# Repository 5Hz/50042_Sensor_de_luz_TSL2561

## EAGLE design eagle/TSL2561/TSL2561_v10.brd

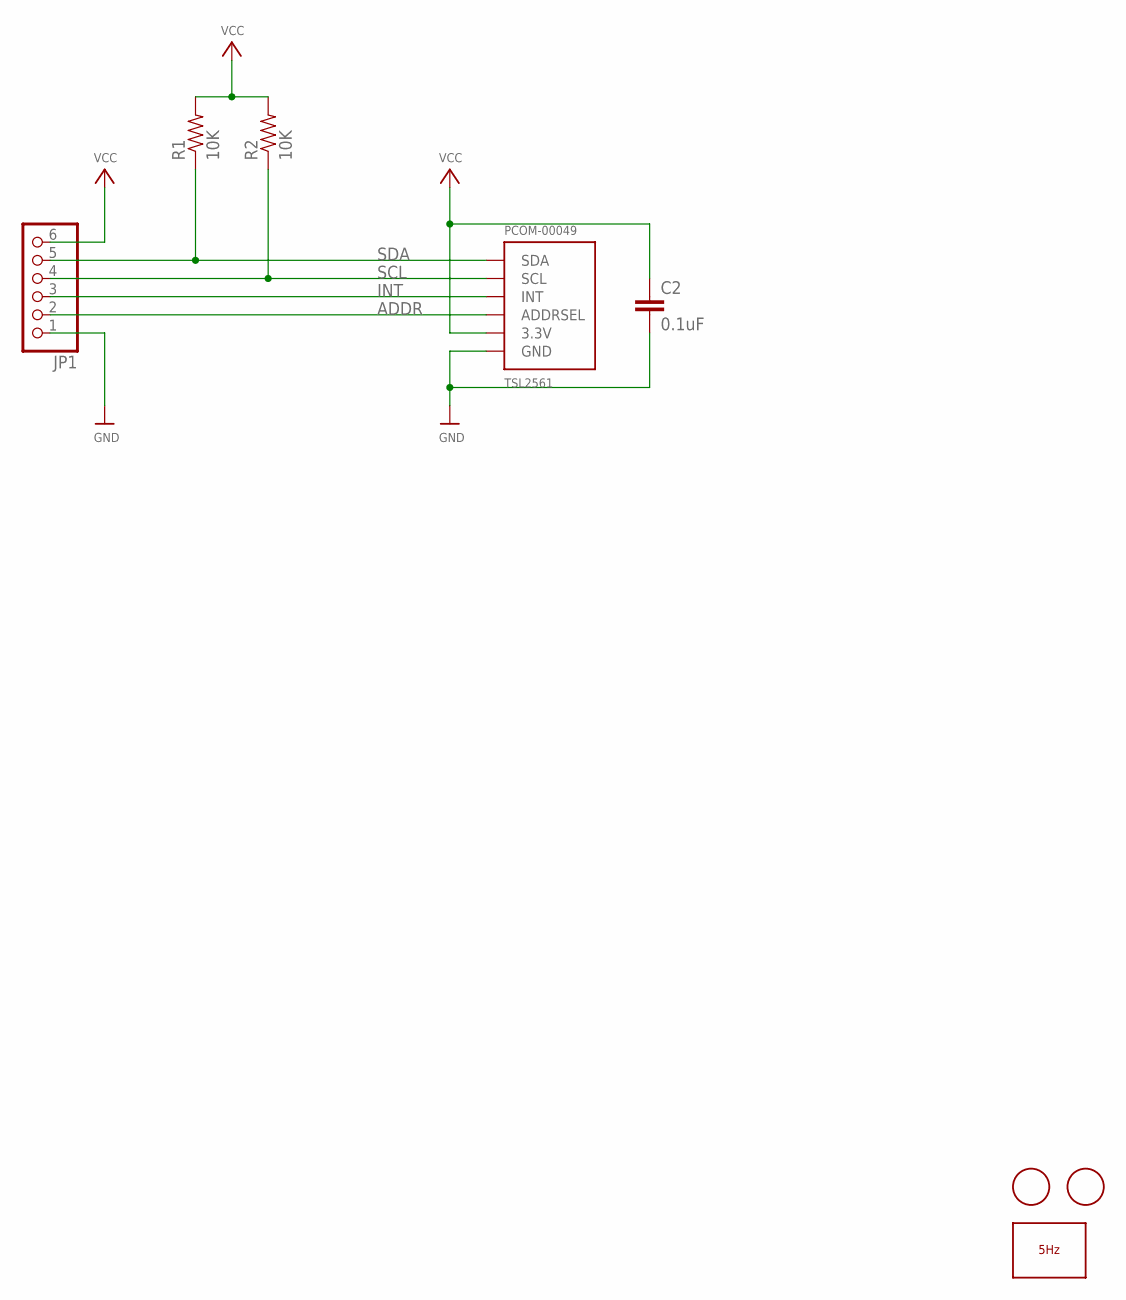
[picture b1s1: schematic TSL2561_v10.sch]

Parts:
C2: 0.1uF; 0603-CAP
JP1: HEADER-1X676MIL; 1X06_ROUND_76
LOGO1: LOGO_5HZ_MAIN_10MM; 5HZ_LOGO_MAIN_10MM
PCOM-00049: TSL2561; TSL2561_FN
R1, R2: 10K; 0603-RES
U$5, U$6: MOUNTINGHOLE2.0; MOUNTINGHOLE_2.0_PLATED

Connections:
ADDR: JP1.2, PCOM-00049.ADR (ADDRSEL)
GND: C2.2, JP1.1, PCOM-00049.VSS (GND)
INT: JP1.3, PCOM-00049.INT
SCL: JP1.4, PCOM-00049.CLK (SCL), R2.1
SDA: JP1.5, PCOM-00049.DATA (SDA), R1.1
VCC: C2.1, JP1.6, PCOM-00049.VDD (3.3V), R1.2, R2.2

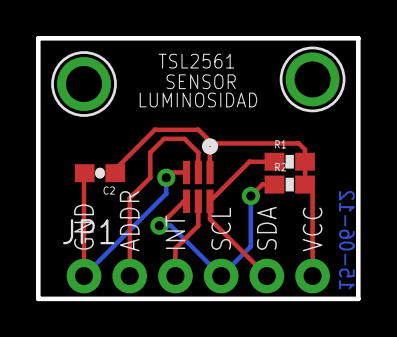
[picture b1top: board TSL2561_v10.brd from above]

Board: 2 copper layers, 17.8 x 14.5 mm, 8 parts (1 on the bottom side), 6 nets.

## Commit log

2014-01-10 creación
